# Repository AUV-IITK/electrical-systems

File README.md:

# electrical-systems
# PURPOSE
The boost converter is Dc to Dc step up volatage while stepping dowm current. It is mainly used to reduce the voltage ripples in the input side(battery) to produce constant Dc output.
# SPECS
- Input Voltage range-14.8 to 16.8 volts
- DC output-19 volts
- output current- 3A
- Ambient Temp-30degree Centigrade
- base_pn-TPS55340-Q1

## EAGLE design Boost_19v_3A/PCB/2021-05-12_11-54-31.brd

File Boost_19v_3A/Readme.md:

# Boost Converter for the NUC

 The simulation has been run on TINA-TI Spice software. Download from here [Link](http://www.ti.com/tool/TINA-TI).

 Results of a simulation on the [Webench](https://webench.ti.com/power-designer/) have been placed in the in the simulation output folder. 

 To run simulation download the schematic and open with TINA-TI.

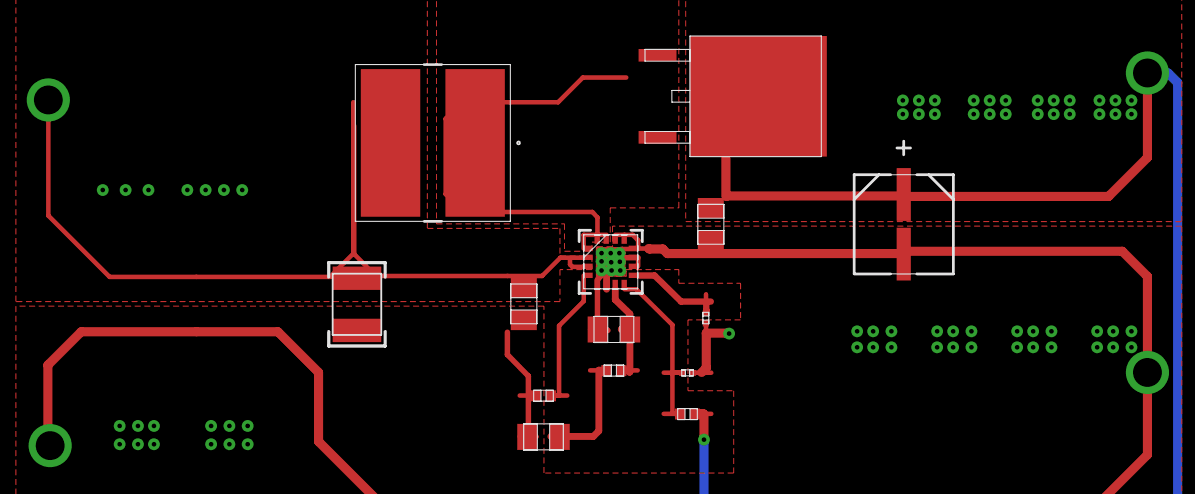
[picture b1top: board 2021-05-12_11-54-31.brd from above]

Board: 4 copper layers, 18 parts (0 on the bottom side), 10 nets.

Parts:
Ccomp, Ccomp2: 0805
Cin: 1210
Cinx: 0805
Cout: CAPSMT_62_E61
Coutx: 0805
Css: 0402
D1: DPAK
GND, GND1: TP-5012
L1: VLP8040
Rcomp: 0402
Rfbb: 0201
Rfbt: 0402
Rt: 0201
U1: S-PWQFN-N16
Vin: TP-5012
Vout: TP-5012

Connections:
0: Ccomp.2, Ccomp2.1, Cin.2, Cinx.2, Cout.2, Coutx.2, Css.2, GND.1, GND1.1, Rfbb.2, Rt.2, U1.5, U1.6, U1.11, U1.12, U1.13, U1.17
1: Cin.1, Cinx.1, L1.1, U1.2, U1.3, Vin.1
2: Css.1, U1.4
3: Rfbb.1, Rfbt.2, U1.8
4: Ccomp2.2, Rcomp.2, U1.7
5: D1.1, D1.3, L1.2, U1.1, U1.15, U1.16
6: Rt.1, U1.9
8: Ccomp.1, Rcomp.1
9: Cout.1, Coutx.1, D1.2, Rfbt.1, Vout.1
S$10netdata: U1.10, U1.14

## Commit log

2020-04-30 starting repo
2020-04-30 starting repository
2020-04-30 boost converter details
    Added the details and things I found about the boost converter design.
2020-04-30 spliting branch Boost_19v_3A
2020-04-30 spliting branch_Buck_5v_5A
2020-04-30 Revert "spliting branch_Buck_5v_5A"
2020-04-30 restructuring repo
2020-04-30 made branch Boost
2020-04-30 made branch Buck_5-12v
2020-04-30 made branch MCU-Atmega2560
2020-04-30 made branch MCU-Atmega328p
2020-04-30 made branch Electrical-cad
2020-04-30 adding readme to master
2020-04-30 uploading readme file
2020-04-30 uploading readme
2020-04-30 boost_converter_update_01
    Added details about boost covnerter
2020-04-30 boost_converter_update_02
    removed the folders added accidentally
2020-04-30 Revert "Added Boost Converter Details"
2020-04-30 boost_converter_update_01
    Updated the details for the boost converter.
2020-04-30 Boost 19v (#13)
    * boost_converter_update_01
    Added details about boost covnerter
    * Revert "Added Boost Converter Details"
2020-04-30 Revert "Boost 19v (#13)"
    This reverts commit 8f394a97cebce2581ee2f1021dbb35846115baae.
2020-04-30 rebuilded repo
2020-04-30 rebuilded branch
2020-05-09 updating instructions
2020-05-10 Update Boost_19v
    Added the details about the TI-TINA model for the bost converter.
2020-09-05 organising branch Atmega2560
2020-11-17 New commit altogether, ignore previous
2020-11-28 Completed PCB Layout changed Input Connector footprint
2020-12-25 self
2020-12-28 Changed component Inductor->Fuse
2020-12-28 schematic completed
2020-12-30 PCBlayout, Routing, 3DModels, DONE
2020-12-30 logo-png changed
2021-01-10 Removed Trace error
2021-01-17 Create PCB
2021-01-17 Create kicad,sch
2021-01-17 boost converter schematic
2021-01-19 adding Kill_switch_board
2021-01-28 netlist of boost converter
2021-01-28 footprints of boost converter
2021-01-30 project files
2021-01-30 fp-lib table
2021-05-22 new board
2021-05-24 issues resolved
2021-05-24 boost 19_V complete board
2021-05-25 resistance values added to LED
2021-05-25 BMP issue resolved
2021-05-27 boost19v pcb layout updated
2021-05-27 Readme.md update
2021-05-28 boost 19v
2021-05-28 boost19v
2021-05-28 .brd file
2021-06-04 Initiated the PCB layout."
2021-06-04 Adding buck
2021-06-05 Aiwaye
2021-06-06 minor fixes, size reduced
2021-06-06 Intermediate PCB layout completed.
2021-06-07 Power Board completed
2021-06-08 issue resolved
2021-06-08 Added 3D models
2021-06-09 updated power-board and stp file
2021-06-09 Changed the mosfet simulation
2021-06-10 reorganising
2022-03-16 power-trace plane changed, gerber-BOM generated
2022-03-17 added fuse
2023-04-13 Added a Documentation folder
2023-04-15 Hydrophones Testing Vi added
2023-04-15 More docs added
